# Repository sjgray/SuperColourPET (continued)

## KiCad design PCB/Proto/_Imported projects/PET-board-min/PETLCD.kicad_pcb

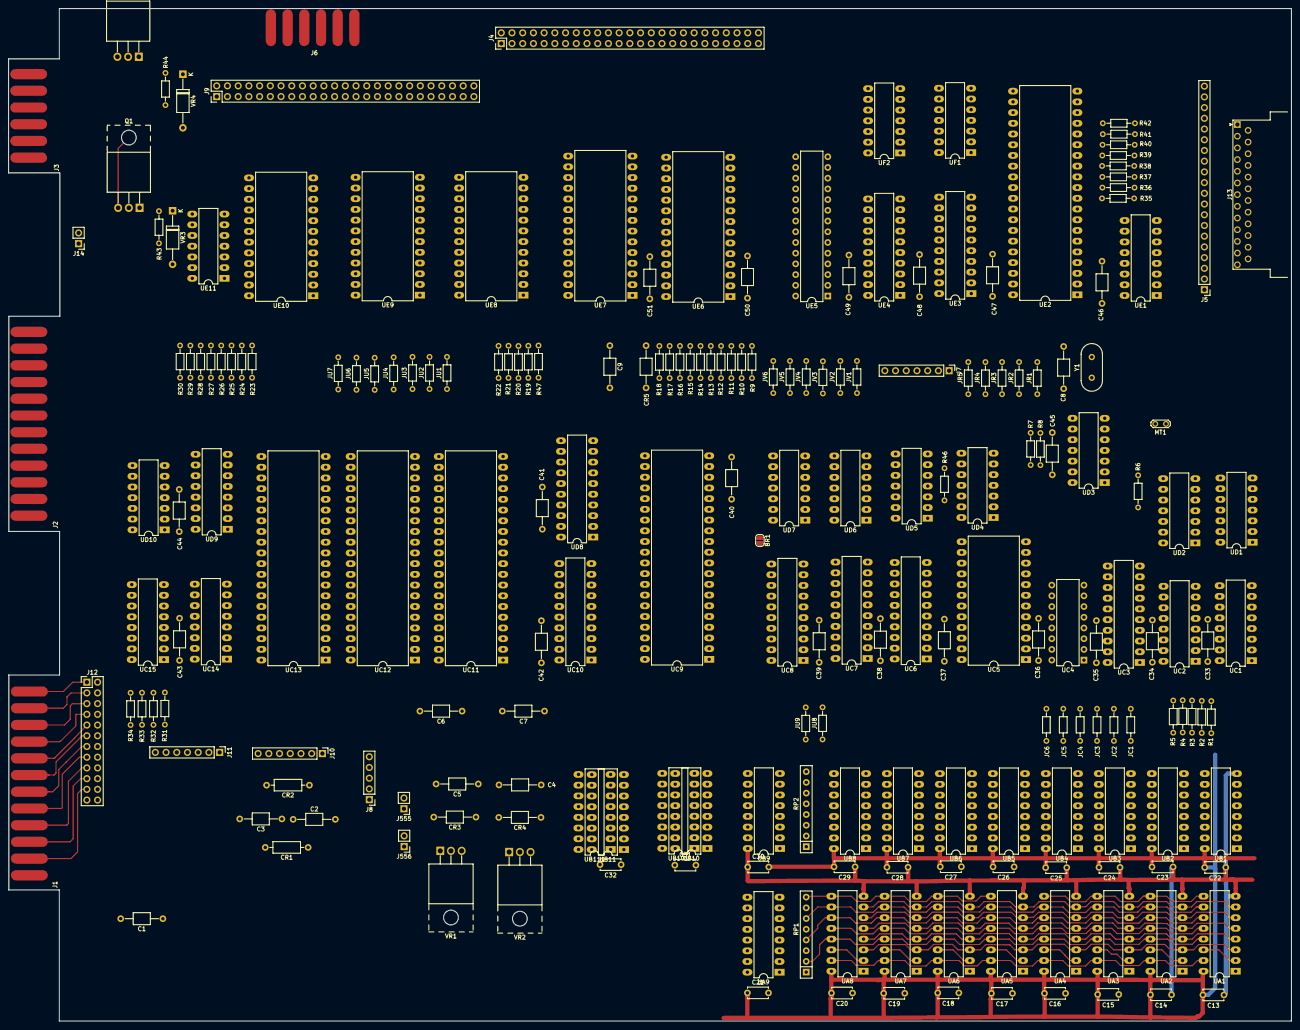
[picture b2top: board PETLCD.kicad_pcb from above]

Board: 2 copper layers, 304.1 x 240.0 mm, 212 parts (0 on the bottom side), 303 nets.

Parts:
BR1: BUBBLE JUMPER; SolderJumper-2_P1.3mm_Open_RoundedPad1.0x1.5mm
C1: 15000u 16V; C_Axial_L3.8mm_D2.6mm_P10.00mm_Horizontal
C2, C3: .22u 50V; C_Axial_L3.8mm_D2.6mm_P10.00mm_Horizontal
C4, C5: 1.0 25V; C_Axial_L3.8mm_D2.6mm_P10.00mm_Horizontal
C6, C7: 47 16V; C_Axial_L3.8mm_D2.6mm_P10.00mm_Horizontal
C8: 22pf; C_Axial_L3.8mm_D2.6mm_P10.00mm_Horizontal
C9: 100pf; C_Axial_L3.8mm_D2.6mm_P10.00mm_Horizontal
C13, C14, C15, C16, C17, C18, C19, C20, C21, C22, C23, C24, C25, C26, C27, C28, C29, C30, C31, C32: 0.1; C_Disc_D4.7mm_W2.5mm_P5.00mm
C33, C34, C35, C36, C37, C38, C39, C40, C41, C42, C43, C44, C45, C46, C47, C48, C49, C50, C51: 0.1; C_Axial_L3.8mm_D2.6mm_P10.00mm_Horizontal
CR1, CR2: 5402; R_Axial_DIN0207_L6.3mm_D2.5mm_P10.16mm_Horizontal
CR3, CR4: 1N5402; C_Axial_L3.8mm_D2.6mm_P10.00mm_Horizontal
CR5: 1N4148; C_Axial_L3.8mm_D2.6mm_P10.00mm_Horizontal
J1, J2: EDGE_CON_02x12; EDGE_CON_24P
J3, J6: EDGE_CON_02x06; EDGE_CON_12P_TAPE
J4, J9: MEMORY EXPANSION; PinHeader_2x25_P2.54mm_Vertical
J5: PET KEYBOARD; PinHeader_1x20_P2.54mm_Vertical
J7: VIDEO OUT; PinHeader_1x07_P2.54mm_Vertical
J8: MAIN POWER; PinHeader_1x05_P2.54mm_Vertical
J10: A/C EXP.; PinHeader_1x07_P2.54mm_Vertical
J11: 9V; PinHeader_1x07_P2.54mm_Vertical
J12: Conn_02x12_Odd_Even; PinHeader_2x12_P2.54mm_Vertical
J13: DB25_Female; DSUB-25_Female_Horizontal_P2.77x2.54mm_EdgePinOffset9.40mm
J14: RESET HEADER; PinHeader_1x02_P2.54mm_Vertical
J555, J556: SWITCHING SUPPLY; PinHeader_1x02_P2.54mm_Vertical
JC1, JC2: PIXEL; R_Axial_DIN0204_L3.6mm_D1.6mm_P7.62mm_Horizontal
JC3: 80COL; R_Axial_DIN0204_L3.6mm_D1.6mm_P7.62mm_Horizontal
JC4: 40 COL; R_Axial_DIN0204_L3.6mm_D1.6mm_P7.62mm_Horizontal
JC5, JC6: .; R_Axial_DIN0204_L3.6mm_D1.6mm_P7.62mm_Horizontal
JR1, JR3: 32K RAM; R_Axial_DIN0204_L3.6mm_D1.6mm_P7.62mm_Horizontal
JR2, JR5: .; R_Axial_DIN0204_L3.6mm_D1.6mm_P7.62mm_Horizontal
JR4: JU; R_Axial_DIN0204_L3.6mm_D1.6mm_P7.62mm_Horizontal
JU1, JU2, JU3, JU4, JU5, JU6, JU7, JU8, JU9: .; R_Axial_DIN0204_L3.6mm_D1.6mm_P7.62mm_Horizontal
JV1, JV2: HSYNC; R_Axial_DIN0204_L3.6mm_D1.6mm_P7.62mm_Horizontal
JV3, JV4: VSYNC; R_Axial_DIN0204_L3.6mm_D1.6mm_P7.62mm_Horizontal
JV5, JV6: PIXEL; R_Axial_DIN0204_L3.6mm_D1.6mm_P7.62mm_Horizontal
MT1: Piezo; TestPoint_2Pads_Pitch2.54mm_Drill0.8mm
Q1, Q2: TIP110; TO-220-3_Horizontal_TabUp
R1, R7, R8: 2.2K; R_Axial_DIN0204_L3.6mm_D1.6mm_P7.62mm_Horizontal
R2, R3, R4, R5, R9, R10, R11, R12, R20, R21, R22, R23, R24, R25, R26, R30, R46, R47: 1K; R_Axial_DIN0204_L3.6mm_D1.6mm_P7.62mm_Horizontal
R6: 10 ohm; R_Axial_DIN0204_L3.6mm_D1.6mm_P7.62mm_Horizontal
R13: 68; R_Axial_DIN0204_L3.6mm_D1.6mm_P7.62mm_Horizontal
R14, R15, R16, R17, R19: 4k7; R_Axial_DIN0204_L3.6mm_D1.6mm_P7.62mm_Horizontal
R18, R35, R36, R37, R38, R39, R40, R41, R42: 10K; R_Axial_DIN0204_L3.6mm_D1.6mm_P7.62mm_Horizontal
R27, R28, R29: 470; R_Axial_DIN0204_L3.6mm_D1.6mm_P7.62mm_Horizontal
R31, R34: 5K1; R_Axial_DIN0204_L3.6mm_D1.6mm_P7.62mm_Horizontal
R32, R33: 2K4; R_Axial_DIN0204_L3.6mm_D1.6mm_P7.62mm_Horizontal
R43, R44: 1.5K; R_Axial_DIN0204_L3.6mm_D1.6mm_P7.62mm_Horizontal
RP1, RP2: R_Pack04_SIP; R_Array_SIP8
UA1, UA2, UA3, UA4, UA5, UA6, UA7, UA8: 4164-2; DIP-16_W7.62mm
UA9: 74LS257; DIP-16_W7.62mm
UB1, UB2, UB3, UB4, UB5, UB6, UB7, UB8: 4164-2; DIP-16_W7.62mm
UB9, UB10, UB11, UB101, UB111: 74LS257; DIP-16_W7.62mm
UC1: 74LS163; DIP-16_W7.62mm
UC2: 74S288; DIP-16_W7.62mm
UC3, UC6, UC7: 74LS374; DIP-20_W7.62mm
UC4: 74166; DIP-16_W7.62mm
UC5: 2332; DIP-24_W15.24mm
UC8: 74LS245; DIP-20_W7.62mm
UC9: 6545; DIP-40_W15.24mm
UC10: 74LS244; DIP-20_W7.62mm
UC11: 6502; DIP-40_W15.24mm
UC12: 6522; DIP-40_W15.24mm
UC13: 6520; DIP-40_W15.24mm
UC14, UC15: MC3446; DIP-16_W7.62mm
UD1, UD4, UD5: 74LS74; DIP-14_W7.62mm
UD2: 74LS00; DIP-14_W7.62mm
UD3: 74LS04; DIP-14_W7.62mm
UD6: 74LS86; DIP-14_W7.62mm
UD7: 74LS14; DIP-14_W7.62mm
UD8: 74LS244; DIP-20_W7.62mm
UD9: MC3446; DIP-16_W7.62mm
UD10: 7417; DIP-14_W7.62mm
UE1: 74LS145; DIP-16_W7.62mm
UE2: 6520; DIP-40_W15.24mm
UE3: 74LS245; DIP-20_W7.62mm
UE4: 74LS273; DIP-20_W7.62mm
UE5: 82S100; DIP-28_W7.62mm
UE6: 82S100; DIP-28_W15.24mm
UE7: 23128; DIP-28_W15.24mm
UE8, UE9, UE10: 2332; DIP-24_W15.24mm
UE11: 7416; DIP-14_W7.62mm
UF1: 74LS02; DIP-14_W7.62mm
UF2: 74LS30; DIP-14_W7.62mm
VR1, VR2: 7805; TO-220F-3_Horizontal_TabUp
VR3, VR4: 7V5; D_A-405_P12.70mm_Horizontal
Y1: 16 MHz; Crystal_HC18-U_Vertical

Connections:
1MHz: UC1.11, UC2.13, UC7.1, UC11.37, UD7.3
02: UC11.39, UD10.1
2MHz: UC1.12, UC2.12
4MHz: UC1.13, UC2.11
5V: C6.1, C7.1, C13.1, C14.1, C15.1, C16.1, C17.1, C18.1, C19.1, C20.1, C22.1, C23.1, C24.1, C25.1, C26.1, C27.1, C28.1, C29.1, C30.1, C31.1, C32.1, C33.1, C34.1, C35.1, C36.1, C37.1, C38.1, C39.1, C40.1, C41.1, C42.1, C43.1, C44.1, C45.1, C46.1, C47.1, C48.1, C49.1, C50.1, C51.1, CR3.2, CR4.2, CR5.1, J8.5, J555.1, J555.2, R1.2, R9.2, R10.2, R11.2, R12.2, R14.2, R15.2, R16.2, R17.2, R18.2, R19.1, R20.1, R21.1, R22.1, R23.2, R24.2, R25.2, R26.2, R27.1, R28.1, R29.1, R30.1, R32.2, R33.2, R35.1, R36.1, R37.1, R38.1, R39.1, R40.1, R41.1, R42.1, R46.2, R47.1, UA1.8, UA2.8, UA3.8, UA4.8, UA5.8, UA6.8, UA7.8, UA8.8, UA9.16, UB1.8, UB2.8, UB3.8, UB4.8, UB5.8, UB6.8, UB7.8, UB8.8, UB9.16, UB10.16, UB11.16, UB101.16, UB111.16, UC1.16, UC2.16, UC3.20, UC4.16, UC5.24, UC6.20, UC7.20, UC8.20, UC9.20, UC10.20, UC11.8, UC12.20, UC13.20, UC14.16, UC15.16, UD2.14, UD3.14, UD6.14, UD7.14, UD8.20, UD9.16, UD10.14, UE1.16, UE2.20, UE3.20, UE4.20, UE5.28, UE6.28, UE7.28, UE8.24, UE9.24, UE10.24, UE11.14, UF1.14, UF2.14, VR1.1, VR2.1
8MHz: JC2.1, UC1.14, UC2.10
9V-UNREG: C1.1, C2.2, C4.1, CR1.1, CR3.1, J11.1, J11.4, J11.6, Q1.2, Q2.2, R43.2, R44.2, VR1.2
16MHz: JC1.1, UC1.2, UC3.11, UD3.1, UD3.8
A0: UC10.15, UC11.9
A1: UC10.8, UC11.10
A2: UC10.13, UC11.11
A3: UC10.11, UC11.12
A4: UC10.17, UC11.13
A5: UC10.6, UC11.14
A6: UC10.4, UC11.15
A7: UC10.2, UC11.16
A8: UC11.17, UD8.17
A9: UC11.18, UD8.15
A10: UC11.19, UD8.13
A11: UC11.20, UD8.11
A12: UC11.22, UD8.8
A13: UC11.23, UD8.6
A14: UC11.24, UD8.4
A15: UC11.25, UD8.2
ATN: J1.11, J12.21
BA0: J9.47, UB11.14, UB111.13, UC9.24, UC10.5, UC12.38, UC13.35, UE2.35, UE7.10, UE8.8, UE9.8, UE10.8, UF1.8
BA1: J9.45, UB11.13, UB111.10, UC10.12, UC12.37, UC13.36, UE2.36, UE7.9, UE8.7, UE9.7, UE10.7, UF1.9
BA2: J9.43, UB11.10, UB111.6, UC10.7, UC12.36, UE7.8, UE8.6, UE9.6, UE10.6, UF1.11
BA3: J9.41, UB11.6, UB111.3, UC10.9, UC12.35, UE7.7, UE8.5, UE9.5, UE10.5, UF1.12
BA4: J9.39, UB11.3, UB101.13, UC10.3, UE2.24, UE7.6, UE8.4, UE9.4, UE10.4, UF2.3
BA5: J9.37, UB10.13, UB101.10, UC10.14, UC13.24, UE7.5, UE8.3, UE9.3, UE10.3, UF2.4
BA6: J9.35, UB10.10, UB101.6, UC10.16, UC12.24, UE7.4, UE8.2, UE9.2, UE10.2, UF2.5
BA7: J9.33, UB10.6, UB101.3, UC10.18, UD2.13, UE7.3, UE8.1, UE9.1, UE10.1, UF2.6
BA8: J9.31, UB10.3, UB111.11, UD8.3, UE6.27, UE7.25, UE8.23, UE9.23, UE10.23
BA9: J9.29, UB11.11, UB111.5, UD8.5, UE6.26, UE7.24, UE8.22, UE9.22, UE10.22
BA10: J9.27, UB11.5, UB111.2, UD8.7, UE6.25, UE7.21, UE8.19, UE9.19, UE10.19
BA11: J9.25, UB11.2, UB101.14, UD8.9, UE5.6, UE6.24, UE7.23, UE8.18, UE9.18, UE10.18
BA12: J9.23, UB10.14, UB101.11, UD8.12, UE5.5, UE6.23
BA13: J9.21, UB10.11, UB111.14, UD8.14, UE5.4, UE6.22, UE7.26
BA14: J9.19, UB10.5, UB101.5, UD8.16, UE5.3, UE6.21
BA15: J9.17, JR4.1, UD8.18, UE5.2, UE6.20
BD0: J4.47, UE3.9, UE7.11, UE8.9, UE9.9, UE10.9
BD1: J4.45, UE3.8, UE7.12, UE8.10, UE9.10, UE10.10
BD2: J4.43, UE3.7, UE7.13, UE8.11, UE9.11, UE10.11
BD3: J4.41, UE3.6, UE7.15, UE8.13, UE9.13, UE10.13
BD4: J4.39, UE3.5, UE7.16, UE8.14, UE9.14, UE10.14
BD5: J4.37, UE3.4, UE7.17, UE8.15, UE9.15, UE10.15
BD6: J4.35, UE3.3, UE7.18, UE8.16, UE9.16, UE10.16
BD7: J4.33, UE3.2, UE7.19, UE8.17, UE9.17, UE10.17
BDRAMRW: R4.1, UA1.3, UA2.3, UA3.3, UA4.3, UA5.3, UA6.3, UA7.3, UA8.3, UB1.3, UB2.3, UB3.3, UB4.3, UB5.3, UB6.3, UB7.3, UB8.3
BRW: J9.7, R29.2, UC8.1, UC9.22, UC12.22, UC13.21, UD10.4, UE5.7, UE6.3, UE11.3, UF1.5
CA1: J2.B, UC12.40
CAS: R5.1, UB1.15, UB2.15, UB3.15, UB4.15, UB5.15, UB6.15, UB7.15, UB8.15
CAS2: R3.1, UA1.15, UA2.15, UA3.15, UA4.15, UA5.15, UA6.15, UA7.15, UA8.15
CASENAII: JR1.2, UD2.1, UE5.11
CASS1_READ: J2.6, UE2.40
CASS2_READ: J2.7, UC12.18
CASS_WRITE: J2.8, UC12.13
CB1: J1.10, J12.19, UC13.18
CB2: J2.M, UC12.19, UD2.9
CHROPTION: UC5.18, UC9.17
CLKVLA: JC5.1, UC3.15, UC6.11, UD7.1
CR7: JR5.2, UE4.19, UE5.27, UE11.5
CS_WFF: UE6.18, UF2.12
D0: UC8.18, UC9.33, UC11.33, UC12.33, UC13.33, UE2.33, UE3.11, UE4.3
D1: UC8.17, UC9.32, UC11.32, UC12.32, UC13.32, UE2.32, UE3.12, UE4.4
D2: UC8.16, UC9.31, UC11.31, UC12.31, UC13.31, UE2.31, UE3.13, UE4.7
D3: UC8.15, UC9.30, UC11.30, UC12.30, UC13.30, UE2.30, UE3.14, UE4.8
D4: UC8.14, UC9.29, UC11.29, UC12.29, UC13.29, UE2.29, UE3.15, UE4.13
D5: UC8.13, UC9.28, UC11.28, UC12.28, UC13.28, UE2.28, UE3.16, UE4.14
D6: UC8.12, UC9.27, UC11.27, UC12.27, UC13.27, UE2.27, UE3.17, UE4.17
D7: UC8.11, UC9.26, UC11.26, UC12.26, UC13.26, UE2.26, UE3.18, UE4.18
DAV: J1.6, J12.11
DIAG: J2.5, J9.11, UC12.12, UD2.10, UD9.5, UE2.9
DIO1: J1.1, J12.1, UC14.2
DIO2: J1.2, J12.3, UC14.14
DIO3: J1.3, J12.5, UC14.6
DIO4: J1.4, J12.7, UC14.10
DIO5: J1.A, J12.2, UC15.2
DIO6: J1.B, J12.4, UC15.14
DIO7: J1.C, J12.6, UC15.6
DIO8: J1.D, J12.8, UC15.10
DISPENA: UC9.18, UD5.2
DOT: UC4.13, UD6.12
DRAMRW: R4.2, UD2.6
DRD0: UA8.2, UA8.14, UB8.2, UB8.14, UC7.3, UC8.2
DRD1: UA7.2, UA7.14, UB7.2, UB7.14, UC7.4, UC8.3
DRD2: UA6.2, UA6.14, UB6.2, UB6.14, UC7.7, UC8.4
DRD3: UA5.2, UA5.14, UB5.2, UB5.14, UC7.8, UC8.5
DRD4: UA4.2, UA4.14, UB4.2, UB4.14, UC7.13, UC8.6
DRD5: UA3.2, UA3.14, UB3.2, UB3.14, UC7.14, UC8.7
DRD6: UA2.2, UA2.14, UB2.2, UB2.14, UC7.17, UC8.8
DRD7: UA1.2, UA1.14, UB1.2, UB1.14, UC7.18, UC8.9
DRMA0: RP2.2, UA1.5, UA2.5, UA3.5, UA4.5, UA5.5, UA6.5, UA7.5, UA8.5, UB1.5, UB2.5, UB3.5, UB4.5, UB5.5, UB6.5, UB7.5, UB8.5
DRMA1: RP2.8, UA1.7, UA2.7, UA3.7, UA4.7, UA5.7, UA6.7, UA7.7, UA8.7, UB1.7, UB2.7, UB3.7, UB4.7, UB5.7, UB6.7, UB7.7, UB8.7
DRMA2: RP2.6, UA1.6, UA2.6, UA3.6, UA4.6, UA5.6, UA6.6, UA7.6, UA8.6, UB1.6, UB2.6, UB3.6, UB4.6, UB5.6, UB6.6, UB7.6, UB8.6
DRMA3: RP2.4, UA1.12, UA2.12, UA3.12, UA4.12, UA5.12, UA6.12, UA7.12, UA8.12, UB1.12, UB2.12, UB3.12, UB4.12, UB5.12, UB6.12, UB7.12, UB8.12
DRMA4: RP1.4, UA1.11, UA2.11, UA3.11, UA4.11, UA5.11, UA6.11, UA7.11, UA8.11, UB1.11, UB2.11, UB3.11, UB4.11, UB5.11, UB6.11, UB7.11, UB8.11
DRMA5: RP1.6, UA1.10, UA2.10, UA3.10, UA4.10, UA5.10, UA6.10, UA7.10, UA8.10, UB1.10, UB2.10, UB3.10, UB4.10, UB5.10, UB6.10, UB7.10, UB8.10
DRMA6: RP1.2, UA1.13, UA2.13, UA3.13, UA4.13, UA5.13, UA6.13, UA7.13, UA8.13, UB1.13, UB2.13, UB3.13, UB4.13, UB5.13, UB6.13, UB7.13, UB8.13
DRMA7: RP1.8, UA1.9, UA2.9, UA3.9, UA4.9, UA5.9, UA6.9, UA7.9, UA8.9, UB1.9, UB2.9, UB3.9, UB4.9, UB5.9, UB6.9, UB7.9, UB8.9
EOI: J1.5, J12.9, R33.1, R34.1, UD10.10
FA12: UE6.11, UE7.2
FA15: JR4.2, UB10.2, UB101.2, UE5.10
GND: C1.2, C4.2, C5.2, C6.2, C7.2, C9.2, C13.2, C14.2, C15.2, C16.2, C17.2, C18.2, C19.2, C20.2, C21.1, C22.2, C23.2, C24.2, C25.2, C26.2, C27.2, C28.2, C29.2, C30.2, C31.2, C32.2, C33.2, C34.2, C35.2, C36.2, C37.2, C38.2, C39.2, C40.2, C41.2, C42.2, C43.2, C44.2, C45.2, C46.2, C47.2, C48.2, C49.2, C50.2, C51.2, J1.12, J1.E, J1.F, J1.H, J1.J, J1.K, J1.L, J1.M, J1.N, J2.1, J2.11, J2.12, J2.A, J2.N, J4.1, J4.2, J4.4, J4.6, J4.8, J4.10, J4.12, J4.14, J4.16, J4.18, J4.20, J4.22, J4.24, J4.26, J4.28, J4.30, J4.32, J4.34, J4.36, J4.38, J4.40, J4.42, J4.44, J4.46, J4.48, J4.49, J4.50, J5.20, J7.2, J7.4, J7.7, J8.2, J9.1, J9.2, J9.4, J9.6, J9.8, J9.10, J9.12, J9.14, J9.16, J9.18, J9.20, J9.22, J9.24, J9.26, J9.28, J9.30, J9.32, J9.34, J9.36, J9.38, J9.40, J9.42, J9.44, J9.46, J9.48, J9.49, J9.50, J10.3, J10.5, J11.5, J11.7, J12.10, J12.12, J12.14, J12.16, J12.18, J12.20, J12.22, J12.23, J12.24, J13.12, J14.2, JC6.1, JR1.1, JR2.1, JR5.1, JU1.1, JU2.1, JU8.1, JV2.1, JV4.1, JV6.1, MT1.2, R13.2, R31.1, R34.2, UA1.16, UA2.16, UA3.16, UA4.16, UA5.16, UA6.16, UA7.16, UA8.16, UA9.8, UB1.16, UB2.16, UB3.16, UB4.16, UB5.16, UB6.16, UB7.16, UB8.16, UB9.8, UB10.8, UB11.8, UB101.8, UB111.8, UC1.3, UC1.4, UC1.5, UC1.6, UC1.8, UC2.8, UC2.15, UC3.1, UC3.10, UC4.1, UC4.6, UC4.8, UC5.12, UC5.20, UC6.10, UC7.10, UC8.10, UC9.1, UC10.1, UC10.10, UC10.19, UC11.1, UC11.21, UC12.1, UC13.1, UC14.4, UC14.8, UC14.12, UC15.4, UC15.8, UC15.12, UD2.7, UD3.3, UD3.5, UD3.7, UD6.7, UD7.7, UD8.1, UD8.10, UD8.19, UD9.4, UD9.8, UD9.12, UD10.7, UE1.8, UE2.1, UE3.10, UE4.10, UE5.1, UE5.14, UE5.19, UE6.1, UE6.14, UE6.19, UE7.14, UE7.22, UE8.12, UE9.12, UE10.12, UE11.7, UF1.7, UF2.7, VR1.3, VR2.3, VR3.2, VR4.2
GNDPWR: C21.2, R13.1
GRAPHIC: BR1.1, UC5.19, UC12.39
HORIZ-DRIVE: J7.5, R10.1, UD6.3
HSYNC: UC9.39, UD6.1
IFC: J1.9, J12.17, R31.2, R32.1, UD10.12
INIT: R46.1, UC5.21, UD4.1
IO_PULLUP: R30.2, UA9.3, UC13.22, UE2.22
KEYA: UE1.15, UE2.2
KEYB: UE1.14, UE2.3
KEYC: UE1.13, UE2.4
KEYD: UE1.12, UE2.5
KIN0: J5.1, J13.14, R35.2, UE2.10
KIN1: J5.2, J13.15, R36.2, UE2.11
KIN2: J5.3, J13.16, R37.2, UE2.12
KIN3: J5.4, J13.17, R38.2, UE2.13
KIN4: J5.5, J13.18, R39.2, UE2.14
KIN5: J5.6, J13.19, R40.2, UE2.15
KIN6: J5.7, J13.20, R41.2, UE2.16
KIN7: J5.8, J13.21, R42.2, UE2.17
KOUT0: J5.9, J13.1, UE1.1
KOUT1: J5.10, J13.2, UE1.2
KOUT2: J5.11, J13.3, UE1.3
KOUT3: J5.12, J13.4, UE1.4
KOUT4: J5.13, J13.5, UE1.5
KOUT5: J5.14, J13.6, UE1.6
KOUT6: J5.15, J13.7, UE1.7
KOUT7: J5.16, J13.8, UE1.9
KOUT8: J5.17, J13.9, UE1.10
KOUT9: J5.18, J13.10, UE1.11
LSD0: UC5.5, UC6.2, UC7.2
LSD1: UC5.4, UC6.5, UC7.5
LSD2: UC5.3, UC6.6, UC7.6
LSD3: UC5.2, UC6.9, UC7.9
LSD4: UC5.1, UC6.12, UC7.12
LSD5: UC5.23, UC6.15, UC7.15
LSD6: UC5.22, UC6.16, UC7.16
LSD7: UC6.19, UC7.19, UD4.2
MA0: UB9.14, UC9.4
MA1: UB9.11, UC9.5
MA2: UB9.5, UC9.6
MA3: UB9.2, UC9.7
MA4: UA9.14, UC9.8
MA5: UA9.11, UC9.9
MA6: UA9.5, UC9.10
MA7: UA9.2, UC9.11
MA8: UB9.10, UC9.12
MA9: UB9.6, UC9.13
MA10: UB9.3, UC9.14
MA11: UA9.13, UC9.15
MA12: JU9.1, UC9.16
MUXA_CRTCLK: UA9.1, UB9.1, UB10.1, UB11.1, UB101.1, UB111.1, UC3.9, UC9.21
NDAC: J1.8, J12.15
NFRD: J1.7, J12.13
NOROW: UC9.35, UD7.5
NO_SCREEN: JR2.2, UE6.4
unnamed: C2.1, CR1.2, J8.1, J10.1, J10.2
unnamed: C3.1, CR2.2, J8.3, J10.6, J10.7, J556.1
unnamed: C3.2, C5.1, CR2.1, CR4.1, J556.2, VR2.2
unnamed: C8.1, R8.1, UD3.9, UD3.10
unnamed: C8.2, Y1.2
unnamed: C9.1, CR5.2, R18.1, UD7.9
unnamed: JC3.1, UC2.7
unnamed: JC3.2, JC4.2, UC3.17
unnamed: JC4.1, UC2.9
unnamed: JC5.2, JC6.2, UB9.13
unnamed: JU6.1, UD10.6
unnamed: JU6.2, JU7.2, R24.1, UF1.6
unnamed: JU7.1, UD10.8
unnamed: JU8.2, JU9.2, UA9.10
unnamed: JV1.2, JV2.2, UD6.2
unnamed: JV3.2, JV4.2, UD6.5
unnamed: JV5.2, JV6.2, UD6.10
unnamed: MT1.1, R6.1
unnamed: Q1.1, R43.1, UE11.10, VR3.1
unnamed: Q2.1, R44.1, UE11.8, VR4.1
unnamed: R1.1, UC1.1, UC1.7, UC1.10, UD1.10, UD1.13
unnamed: R6.2, UD2.8
unnamed: R7.1, R8.2, UD3.11, UD3.12
unnamed: R7.2, UD3.13, Y1.1
unnamed: R25.1, UE7.27, UE8.21, UE9.21, UE10.21
unnamed: UC2.1, UC3.3
unnamed: UC2.2, UC3.4
unnamed: UC2.3, UC3.7
unnamed: UC2.4, UC3.8
unnamed: UC2.5, UC3.13
unnamed: UC2.6, UC3.14
unnamed: UC2.14, UC3.19
unnamed: UC3.2, UD2.2
unnamed: UC3.5, UD1.12
unnamed: UC3.12, UD2.4
unnamed: UC4.2, UC5.9
unnamed: UC4.3, UC5.10
unnamed: UC4.4, UC5.11
unnamed: UC4.5, UC5.13
unnamed: UC4.10, UC5.14
unnamed: UC4.11, UC5.15
unnamed: UC4.12, UC5.16
unnamed: UC4.14, UC5.17
unnamed: UC9.3, UD7.12
unnamed: UC9.25, UD2.11
unnamed: UD2.12, UD7.10
unnamed: UD4.6, UD6.13
unnamed: UD4.12, UF1.1
unnamed: UD5.8, UF1.2
unnamed: UD5.5, UD5.12
unnamed: UD6.11, UF1.3
unnamed: UD7.8, UE11.1, UE11.13
unnamed: UE3.1, UF1.4
unnamed: UE4.2, UE5.20
unnamed: UE4.5, UE5.21
unnamed: UE4.6, UE5.22
unnamed: UE4.9, UE5.23
unnamed: UE4.11, UF2.8
unnamed: UE4.12, UE5.24
unnamed: UE4.15, UE5.25
unnamed: UF1.10, UF2.1
unnamed: UF1.13, UF2.2
PA0: UC13.2, UC14.1
PA1: UC13.3, UC14.15
PA2: UC13.4, UC14.7
PA3: UC13.5, UC14.9
PA4: UC13.6, UC15.1
PA5: UC13.7, UC15.15
PA6: UC13.8, UC15.7
PA7: UC13.9, UC15.9
PB0: UC13.10, UC14.3
PB1: UC13.11, UC14.13
PB2: UC13.12, UC14.5
PB3: UC13.13, UC14.11
PB4: UC13.14, UC15.3
PB5: UC13.15, UC15.13
PB6: UC13.16, UC15.5
PB7: UC13.17, UC15.11
PENSTROBE: BR1.2, J4.9, UD7.13
PHI2: J9.9, R28.2, UC9.23, UC12.25, UC13.25, UD10.2, UE5.8, UE6.2, UF2.11
PIA1_CB2: UE2.19, UE11.11
PIXEL: UD4.8, UD6.9
PIXEL_CLOCK: JC1.2, JC2.2, UC4.7
PULLUP: JV1.1, JV3.1, JV5.1, R9.1, UC4.9, UD4.4, UD4.10, UD5.1, UD5.4, UD5.10, UD5.13
RA4: UA9.6, UC9.34
RDY: J4.5, R21.2, UC11.2
RW: UC11.34, UD10.3
S0: R22.2, UC11.38
SYNC: J9.15, UC11.7
USER0: J2.C, JU3.1, UC12.2
USER1: J2.D, JU4.1, UC12.3
USER2: J2.E, JU5.1, UC12.4
USER3: J2.F, UC12.5
USER4: J2.H, UC12.6
USER5: J2.J, UC12.7
USER6: J2.K, UC12.8
USER7: J2.L, UC12.9
VDRIVE: J2.9, UC12.15, UE2.18
VERT-DRIVE: J7.3, R11.1, UD6.6
VIA_PB4: UC12.14, UE11.9
VIDEO: J2.2, J7.1, R12.1, UD6.8
VSYNC: UC9.40, UD6.4
XA0: RP2.1, UB9.9, UB11.12, UB111.12
XA1: RP2.7, UB9.12, UB11.9, UB111.9
XA2: RP2.5, UB9.7, UB11.7, UB111.7
XA3: RP2.3, UB9.4, UB11.4, UB111.4
XA4: RP1.3, UA9.12, UB10.12, UB101.12
XA5: RP1.5, UA9.9, UB10.9, UB101.9
XA6: RP1.1, UA9.7, UB10.7, UB101.7
XA7: RP1.7, UA9.4, UB10.4, UB101.4
~16MHz: UD1.11, UD3.2
~ATN_IN: UC13.40, UD9.7
~BRAS: R2.1, UA1.4, UA2.4, UA3.4, UA4.4, UA5.4, UA6.4, UA7.4, UA8.4, UB1.4, UB2.4, UB3.4, UB4.4, UB5.4, UB6.4, UB7.4, UB8.4
~BRW: J9.5, R27.2, UD2.5, UE11.4
~CASENA1: UE5.9, UE6.10
~CASI: R5.2, UC3.6
~CASII: R3.2, UD2.3
~CLKVLA: UC7.11, UD5.3, UD7.2
~CS_9: UD10.5, UE6.17, UE10.20
~CS_A: UD10.9, UE6.16, UE9.20
~CS_E: UE6.13, UE8.20
~CS_IO: UC12.23, UD7.11, UE2.23, UE6.15
~CS_K+B: UE6.12, UE7.20
~DAV_IN: UC12.17, UD9.1
~DAV_OUT: UC13.19, UD9.3
~ENDRA: JR3.2, UC8.19, UE5.13
~IRQ: J9.13, R19.2, UC11.4, UC12.21, UC13.37, UC13.38, UE2.37, UE2.38
~LOADSR: UC3.16, UC4.15, UD4.3, UD5.11
~NDAC_IN: UC12.10, UD9.9
~NDAC_OUT: UC13.39, UD9.11
~NMI: J4.3, R20.2, UC11.6
~NOROM: J4.11, R47.2, UC11.5, UE6.9, UE11.6
~NOROW: UD4.13, UD7.6
~NO_IO: R14.1, UE4.16, UE5.26, UE6.5
~NRFD_IN: UC12.16, UD9.15
~NRFD_OUT: UC12.11, UD9.13
~PHI0: UC6.1, UD7.4
~RAMON: J4.23, JU5.2, R17.1, UE6.8
~RAMSEL_9: JU2.2, JU4.2, R16.1, UE6.7
~RAMSEL_A: JU1.2, JU3.2, R15.1, UE6.6
~RAS: R2.2, UD1.9
~RES: J4.7, J14.1, R26.1, UC11.40, UC12.34, UC13.34, UD10.13, UE4.1, UE11.12
~RESCRT: R23.1, UC9.2, UE11.2

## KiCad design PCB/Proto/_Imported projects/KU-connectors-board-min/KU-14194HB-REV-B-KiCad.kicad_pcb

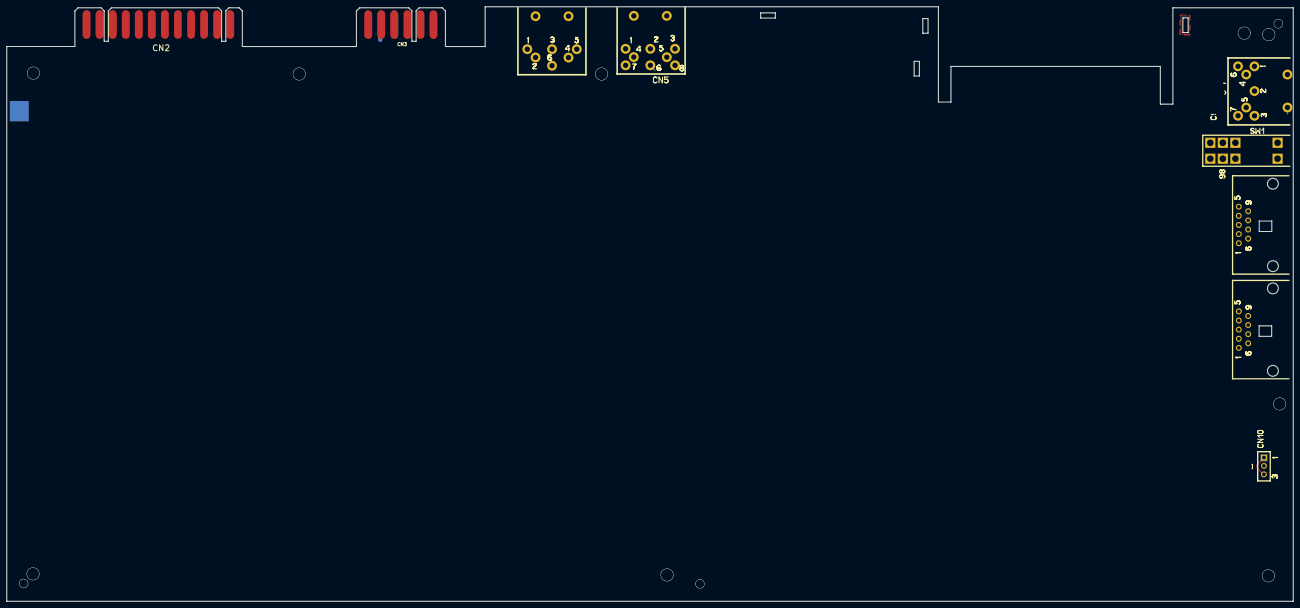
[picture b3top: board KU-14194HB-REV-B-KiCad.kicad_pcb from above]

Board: 2 copper layers, 390.2 x 180.3 mm, 9 parts (0 on the bottom side), 7 nets.

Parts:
CN2: USER_PORT_CON; EDGE_CON_24P
CN3: CASSETTE_PORT_CON; EDGE_CON_12P_TAPE
CN4: SERIAL_BUS_CON; SERIAL_CON_DIN6
CN5: AV_CONN; AV_CON_DIN8
CN7: POWER_CON; POWER_CON_DIN7
CN8, CN9: CONTROL_PORT; JOYPORT_DB9
CN10: LED_CONNECTOR; LED_CON
SW1: POWER_SWITCH

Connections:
/Sheet1/5V_joyport: CN8.7, CN9.7
/Sheet1/CASS_RD: CN3.D,4, CN4.1
/Sheet1/LED+: CN10.1, CN10.3
Earth: CN2.1, CN2.12, CN2.A, CN2.N, CN3.A,1, CN4.2, CN5.2, CN7.1, CN7.2, CN7.3, CN8.8, CN9.8
unnamed: CN7.4, CN7.5, SW1.5
unnamed: CN7.6, SW1.2
~RESET: CN2.3, CN4.6

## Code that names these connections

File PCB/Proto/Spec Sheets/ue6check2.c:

#include <stdio.h>

/* define input parameters */

#define	I0(i)		(i & 1)
#define I1(i)		((i >> 1) & 1)
#define I2(i)		((i >> 2) & 1)
#define I3(i)		((i >> 3) & 1)
#define I4(i)		((i >> 4) & 1)
#define I5(i)		((i >> 5) & 1)
#define I6(i)		((i >> 6) & 1)
#define I7(i)		((i >> 7) & 1)
#define I8(i)		((i >> 8) & 1)
#define I9(i)		((i >> 9) & 1)
#define I10(i)		((i >> 10) & 1)
#define I11(i)		((i >> 11) & 1)
#define I12(i)		((i >> 12) & 1)
#define I13(i)		((i >> 13) & 1)
#define I14(i)		((i >> 14) & 1)
#define I15(i)		((i >> 15) & 1)

/* map input to signals */

#define NOROM(i)	(!I0(i))
#define RAMON(i)	(!I1(i))
#define RAMSEL9(i)	(!I2(i))
#define RAMSELA(i)	(!I3(i))
#define NOIO(i)		(!I4(i))
#define NOSCREEN(i)	I5(i)
#define BRW(i)		I6(i)
#define PHI2(i)		I7(i)
#define BA8(i)		I8(i)
#define BA9(i)		I9(i)
#define BA10(i)		I10(i)
#define BA11(i)		I11(i)
#define BA12(i)		I12(i)
#define BA13(i)		I13(i)
#define BA14(i)		I14(i)
#define BA15(i)		I15(i)

/* calculate output signals */

#define CSWFF(i)	(BA8(i) && BA9(i) && BA10(i) && BA11(i) && BA12(i) && BA13(i) && BA14(i) && BA15(i) && (!BRW(i)))

#define CS9(i)		(BA12(i) && !BA13(i) && !BA14(i) && BA15(i) && !NOROM(i) && !RAMON(i) && !RAMSEL9(i))

#define CSA(i)		(!BA12(i) && BA13(i) && !BA14(i) && BA15(i) && !NOROM(i) && !RAMON(i) && !RAMSELA(i))

#define CSIO(i)		(!BA8(i) && !BA9(i) && !BA10(i) && BA11(i) && !BA12(i) && BA13(i) && BA14(i) && BA15(i) && ( \
			  !NOIO(i) \
			  || (!NOROM(i) && !RAMON(i)) \
			  || (!NOROM(i) && !RAMSELA(i)) \
			))
			
#define CSE(i)		(BRW(i) && !BA12(i) && BA13(i) && BA14(i) && BA15(i) && ( \
			  (!NOROM(i) && ( \
			    BA8(i) \
			    || BA9(i) \
			    || BA10(i) \
			    || !BA11(i) \
			  ) && ( \
			    !RAMON(i) \
			    || (!RAMSEL9(i) && !RAMSELA(i)) \
			  )) \
			  || (NOROM(i) && !NOIO(i) && BA11(i) && ( \
			    BA8(i) \
			    || BA9(i) \
			    || BA10(i) \
			  )) \
			))
	
#define CSKB(i)		(!NOROM(i) && BRW(i) && BA15(i) && ( \
			  (!RAMON(i) && !BA13(i) && BA14(i)) \
			  || (!RAMON(i) && BA12(i) && BA13(i)) \
			  || (!RAMSELA(i) && BA12(i) && BA13(i) && BA14(i)) \
			))

#define FA12(i)		(! \
			  (!NOROM(i) && !RAMON(i) && BRW(i) && BA15(i) && ( \
			    (!BA12(i) && !BA13(i) && BA14(i)) \
			    || (BA12(i) && BA13(i) && !BA14(i)) \
			  )) \
			)

#define CASENAI(i)	(PHI2(i) && ( \
			  !BA15(i) \
			  || (!NOSCREEN(i) && !BA12(i) && !BA13(i) && !BA14(i)) \
			  || (!NOROM(i) && ( \
			    (!BA12(i) && !BA13(i) && !BA14(i)) \
			    || (RAMSEL9(i) && !BA13(i) && !BA14(i)) \
			    || (RAMSELA(i) && !BA12(i) && !BA14(i)) \
			    || (RAMON(i) && ( \
			      !BA14(i) \
			      || !BA13(i) \
			      || (RAMSEL9(i) && !BA12(i) && ( \
				BA8(i) \
				|| BA9(i) \
				|| BA10(i) \
				|| !BA11(i) \
			      )) \
			      || (RAMSELA(i) && ( \
				BA8(i) \
				|| BA9(i) \
				|| BA10(i) \
				|| !BA11(i) \
				|| BA12(i) \
				|| NOIO(i) \
			      )) \
			    )) \
			    || (!BRW(i) && ( \
			      !BA14(i) \
			      || !BA13(i) \
			      || BA12(i) \
			      || !BA11(i) \
			      || BA10(i) \
			      || BA9(i) \
			      || BA8(i) \
			    )) \
			  )) \
			))

	
/* map output to logical lines */

#define F0(i)		CSWFF(i)
#define F1(i)		(!CS9(i))
#define F2(i)		(!CSA(i))
#define F3(i)		(!CSIO(i))
#define F4(i)		(!CSE(i))
#define F5(i)		(!CSKB(i))
#define F6(i)		FA12(i)
#define F7(i)		(!CASENAI(i))


int main(int argc, char *argv[]) {

	int i;
	unsigned int b;
	
	for(i=0;i<65536;i++) {
	  b=0;

	  if ( F0(i) ) {
	    b|=1;
	  }
	  if ( F1(i) ) {
	    b|=2;
	  }
	  if ( F2(i) ) {
	    b|=4;
	  }
	  if ( F3(i) ) {
	    b|=8;
	  }
	  if ( F4(i) ) {
	    b|=16;
	  }
	  if ( F5(i) ) {
	    b|=32;
	  }
	  if ( F6(i) ) {
	    b|=64;
	  }
	  if ( F7(i) ) {
	    b|=128;
	  }
	  printf("%c",b);
	}

	return 0;
}

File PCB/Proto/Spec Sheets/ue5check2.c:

#include <stdio.h>

/* define input parameters */

#define	I0(i)		(i & 1)
#define I1(i)		((i >> 1) & 1)
#define I2(i)		((i >> 2) & 1)
#define I3(i)		((i >> 3) & 1)
#define I4(i)		((i >> 4) & 1)
#define I5(i)		((i >> 5) & 1)
#define I6(i)		((i >> 6) & 1)
#define I7(i)		((i >> 7) & 1)
#define I8(i)		((i >> 8) & 1)
#define I9(i)		((i >> 9) & 1)
#define I10(i)		((i >> 10) & 1)
#define I11(i)		((i >> 11) & 1)
#define I12(i)		((i >> 12) & 1)
#define I13(i)		((i >> 13) & 1)
#define I14(i)		((i >> 14) & 1)
#define I15(i)		((i >> 15) & 1)

/* map input to signals */

#define CASENAI(i)	I0(i)
#define PHI2(i)		I1(i)
#define BRW(i)		I2(i)
#define BA11(i)		I3(i)
#define BA12(i)		I4(i)
#define BA13(i)		I5(i)
#define BA14(i)		I6(i)
#define BA15(i)		I7(i)
#define CR7_ENABLE(i)	I8(i)
#define CR6_IOPEEK(i)	I9(i)
#define CR5_SCRPEEK(i)	I10(i)
#define CR4_RES(i)	I11(i)
#define CR3_HIBLK(i)	I12(i)
#define CR2_LOBLK(i)	I13(i)
#define CR1_HIWP(i)	I14(i)
#define CR0_LOWP(i)	I15(i)

/* calculate output signals */

#define FA15(i)		((BA15(i) && !CR7_ENABLE(i)) \
			|| (!BA12(i) && !BA13(i) && !BA14(i) && BA15(i) && CR5_SCRPEEK(i)) \
			|| (!BA14(i) && BA15(i) && CR2_LOBLK(i)) \
			|| (BA14(i) && BA15(i) && CR3_HIBLK(i)) \
			|| (BA11(i) && !BA12(i) && BA13(i) && BA14(i) && BA15(i) && CR6_IOPEEK(i)) )

#define CASENAII(i)	((CASENAI(i) && PHI2(i) && BA15(i) && CR7_ENABLE(i)) && ( \
			  (BRW(i) && (	\
			    (!BA13(i) && !CR5_SCRPEEK(i)) \
			    || (BA12(i)) \
			    || (!BA13(i) && BA14(i)) \
			    || (!BA14(i) && BA13(i)) \
			    || (!BA11(i) && BA14(i)) \
			    || (BA14(i) && !CR6_IOPEEK(i)) \
			  )) \
			  || (BA14(i) && !BA11(i) && !CR1_HIWP(i)) \
			  || (BA14(i) && BA12(i) && !CR1_HIWP(i)) \
			  || (BA14(i) && !BA13(i) && !CR1_HIWP(i)) \
			  || (BA14(i) && !CR6_IOPEEK(i) && !CR1_HIWP(i)) \
			  || (!BA14(i) && BA12(i) && !CR0_LOWP(i)) \
			  || (!BA14(i) && BA13(i) && !CR0_LOWP(i)) \
			  || (!BA14(i) && !CR5_SCRPEEK(i) && !CR0_LOWP(i)) \
			))

#define NOSCREEN(i)	(CR7_ENABLE(i) && !CR5_SCRPEEK(i))

#define ENDRA(i)	( \
			  (!CASENAI(i) && PHI2(i)) \
			  || (PHI2(i) && BA15(i) && CR7_ENABLE(i) && ( \
			      (BRW(i) && ( \
			          (!BA13(i) && !CR5_SCRPEEK(i)) \
			          || BA12(i) \
			          || (!BA13(i) && BA14(i)) \
			          || (!BA14(i) && BA13(i)) \
			          || (!BA11(i) && BA14(i)) \
			          || (BA14(i) && !CR6_IOPEEK(i)) \
			        ) \
			      ) \
			      || (BA14(i) && !BA11(i) && !CR1_HIWP(i)) \
			      || (BA14(i) && BA12(i) && !CR1_HIWP(i)) \
			      || (BA14(i) && !BA13(i) && !CR1_HIWP(i)) \
			      || (BA14(i) && !CR6_IOPEEK(i) && !CR1_HIWP(i)) \
			      || (!BA14(i) && BA12(i) && !CR0_LOWP(i)) \
			      || (!BA14(i) && BA13(i) && !CR0_LOWP(i)) \
			      || (!BA14(i) && !CR5_SCRPEEK(i) && !CR0_LOWP(i)) \
			    ) \
			  ) \
			)
		
/* map output to logical lines */

#define F4(i)		(!ENDRA(i))
#define F5(i)		NOSCREEN(i)
#define F6(i)		CASENAII(i)
#define F7(i)		FA15(i)	  


int main(int argc, char *argv[]) {

	int i;
	unsigned int b;
	
	for(i=0;i<65536;i++) {
	  b=0;

	  if (     ((i & 0x0182) == 0x0080)
		|| ((i & 0x0181) == 0x0081)
		|| ((i & 0x04f2) == 0x0480)
		|| ((i & 0x04f1) == 0x0481)
		|| ((i & 0x24c2) == 0x2480)
		|| ((i & 0x14c2) == 0x14c0)
		|| ((i & 0xa4c5) == 0xa481)
		|| ((i & 0x06fa) == 0x06e8)
		|| ((i & 0x54c5) == 0x54c1)
		|| ((i & 0x06f9) == 0x06e9)
	  ) {
	    b|=1;
	  }
	  if (     ((i & 0x0182) == 0x0080)
		|| ((i & 0x0181) == 0x0081)
		|| ((i & 0x04f2) == 0x0480)
		|| ((i & 0x04f1) == 0x0481)
		|| ((i & 0x24c2) == 0x2480)
		|| ((i & 0x14c2) == 0x14c0)
		|| ((i & 0xa4c5) == 0xa481)
		|| ((i & 0x06fa) == 0x06e8)
		|| ((i & 0x54c5) == 0x54c1)
		|| ((i & 0x06f9) == 0x06e9)
	  ) {
	    b|=2;
	  }
	  if (     ((i & 0x0182) == 0x0080)
		|| ((i & 0x0181) == 0x0081)
		|| ((i & 0x04f2) == 0x0480)
		|| ((i & 0x04f1) == 0x0481)
		|| ((i & 0x24c2) == 0x2480)
		|| ((i & 0x14c2) == 0x14c0)
		|| ((i & 0xa4c5) == 0xa481)
		|| ((i & 0x06fa) == 0x06e8)
		|| ((i & 0x54c5) == 0x54c1)
		|| ((i & 0x06f9) == 0x06e9)
	  ) {
	    b|=4;
	  }
	  if (     ((i & 0x0182) == 0x0080)
		|| ((i & 0x0181) == 0x0081)
		|| ((i & 0x04f2) == 0x0480)
		|| ((i & 0x04f1) == 0x0481)
		|| ((i & 0x24c2) == 0x2480)
		|| ((i & 0x14c2) == 0x14c0)
		|| ((i & 0xa4c5) == 0xa481)
		|| ((i & 0x06fa) == 0x06e8)
		|| ((i & 0x54c5) == 0x54c1)
		|| ((i & 0x06f9) == 0x06e9)
	  ) {
	    b|=8;
	  }
	  if ( F4(i) ) {
	    b|=16;
	  }
	  if ( F5(i) ) {
	    b|=32;
	  }
	  if ( F6(i) ) {
	    b|=64;
	  }
	  if ( F7(i) ) {
	    b|=128;
	  }
	  b^=(1|2|4|8);
	  printf("%c",b);
	}

	return 0;
}

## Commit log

2024-01-04 PROTO Initial design
    Proto (2023-01-24) PCB designed in Kicad. Untested!!!!!!! Very early design, subject to change!!!!
2024-02-09 Cleanup unused files
    Cleanup
